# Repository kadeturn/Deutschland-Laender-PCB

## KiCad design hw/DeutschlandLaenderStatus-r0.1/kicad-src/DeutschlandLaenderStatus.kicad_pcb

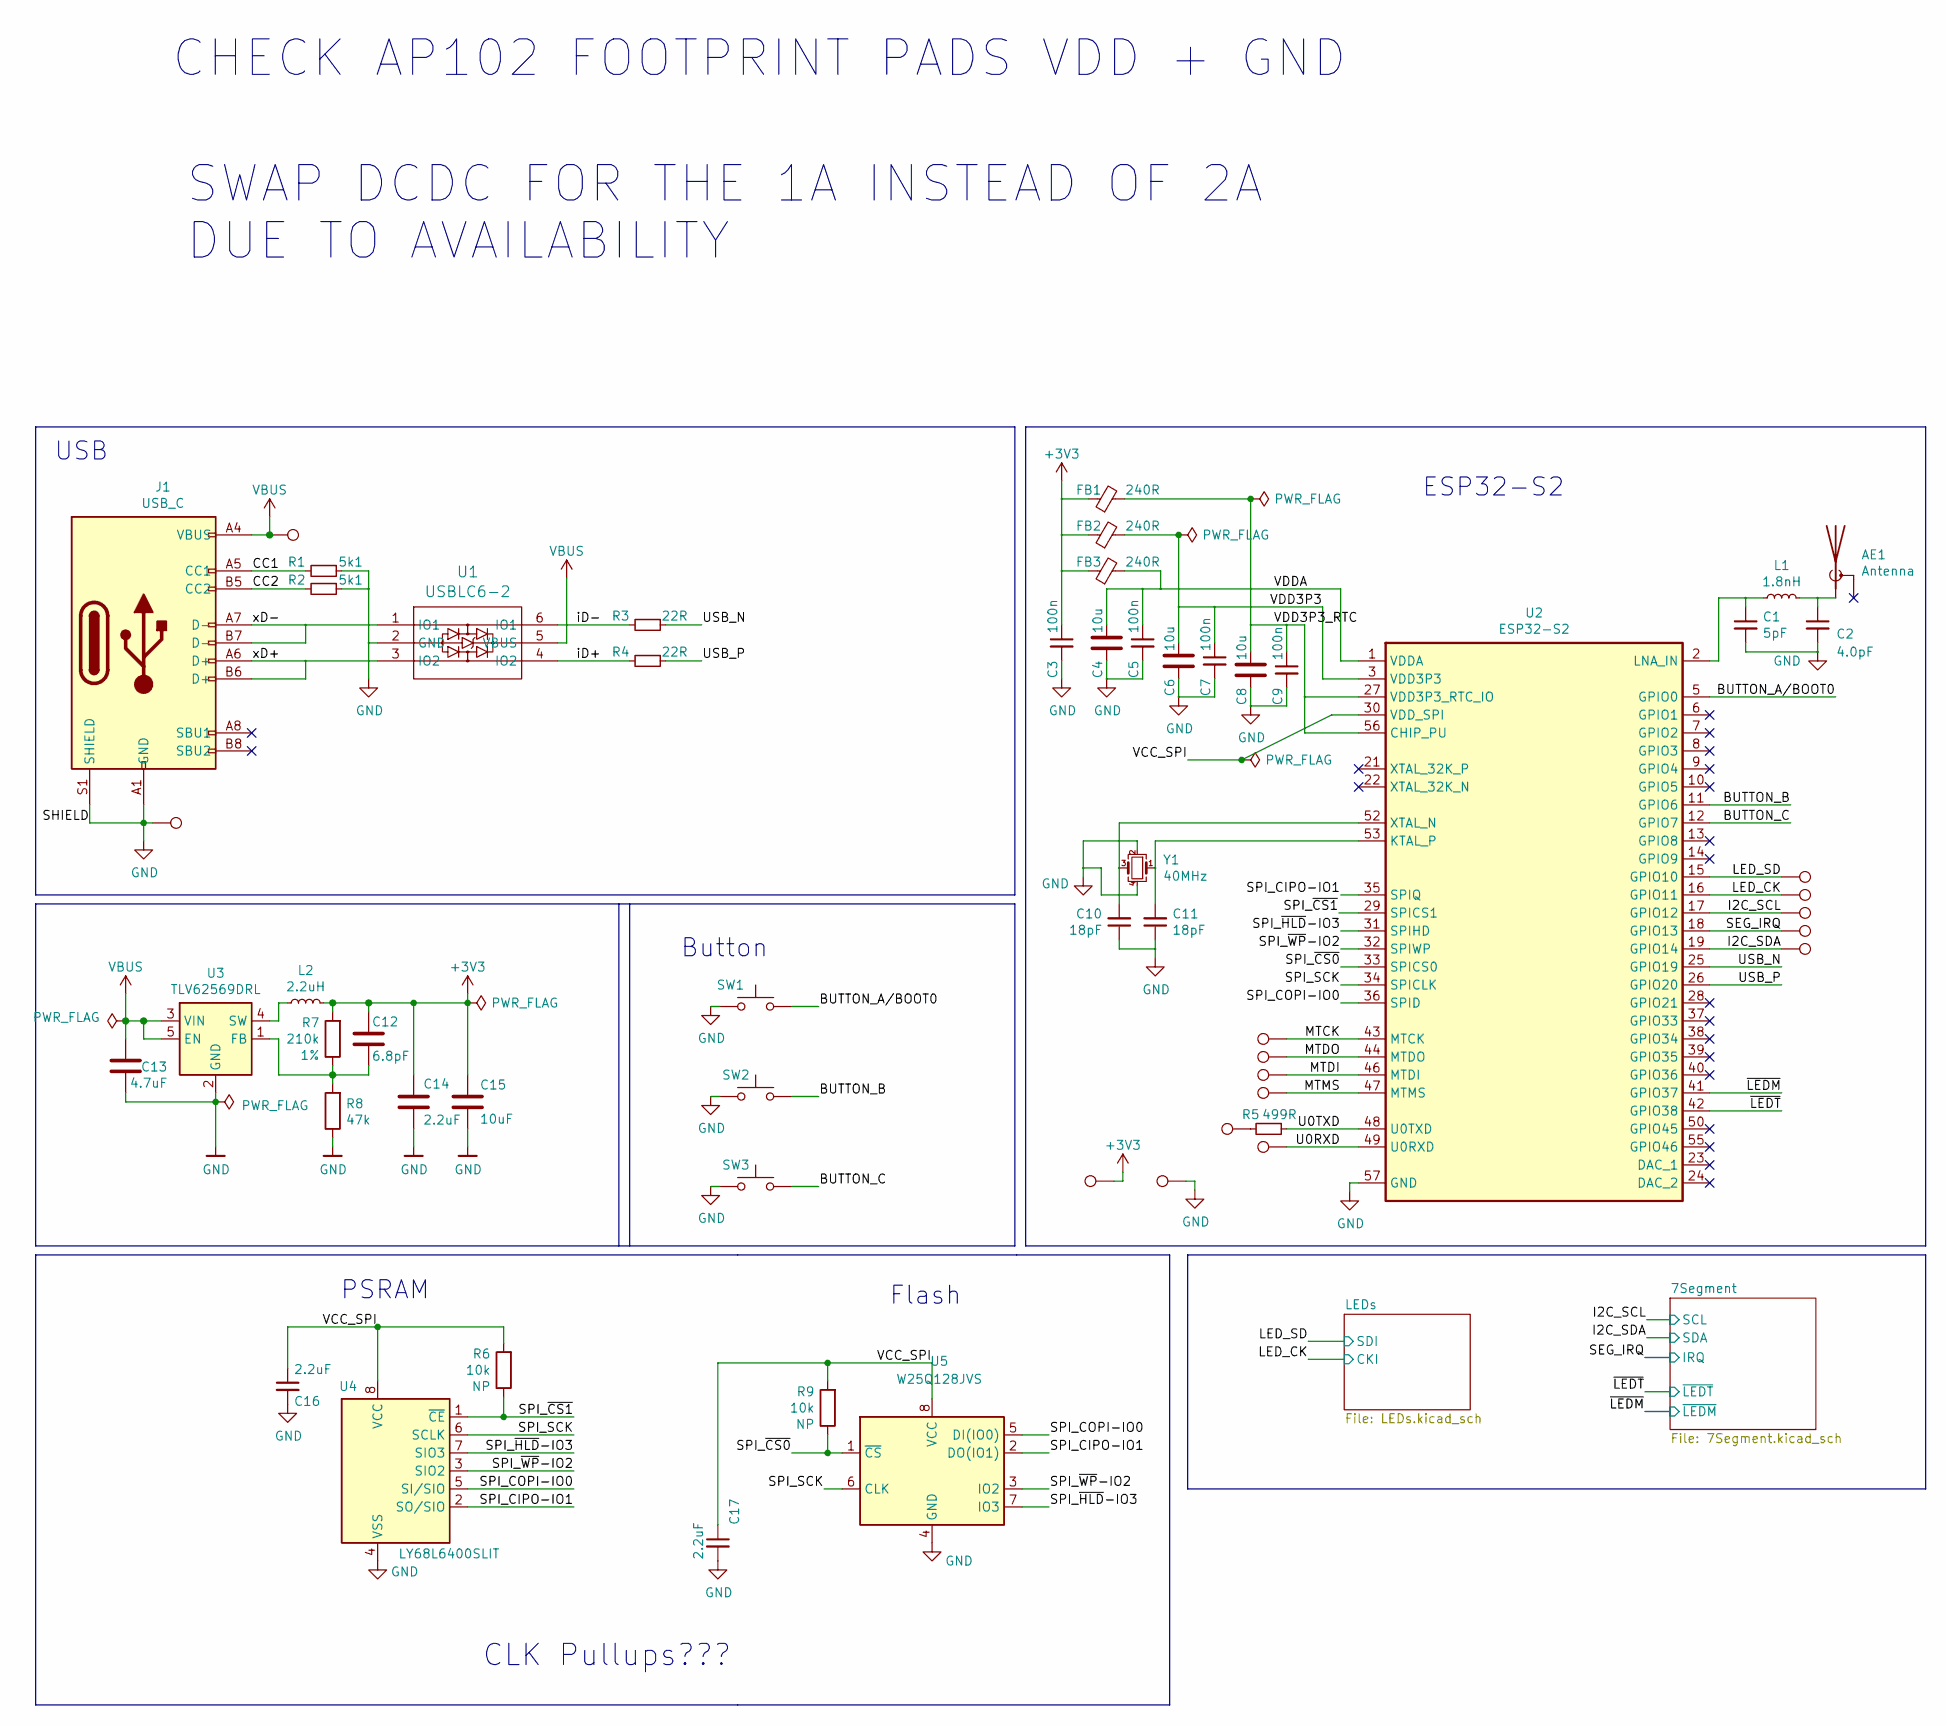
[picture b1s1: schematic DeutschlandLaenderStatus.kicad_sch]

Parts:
AE1: Antenna; Ant_3216
C1: 5pF; C_0402_1005Metric
C2: 4.0pF; C_0402_1005Metric
C3, C5, C7, C9: 100n; C_0402_1005Metric
C4, C6, C8: 10u; C_0603_1608Metric
C10, C11: 18pF; C_0402_1005Metric
C12: 6.8pF; C_0402_1005Metric
C13: 4.7uF; C_0402_1005Metric
C14, C16, C17: 2.2uF; C_0402_1005Metric
C15: 10uF; C_0603_1608Metric
FB1, FB2, FB3: 240R; L_0402_1005Metric
J1: USB_C; USB_C_Receptacle_HRO_TYPE-C-31-M-12
L1: 1.8nH; L_0402_1005Metric
L2: 2.2uH; L_0805_2012Metric
R1, R2: 5k1; R_0402_1005Metric
R3, R4: 22R; R_0402_1005Metric
R5: 499R; R_0402_1005Metric
R6, R9: 10k; R_0402_1005Metric
R7: 210k; R_0402_1005Metric
R8: 47k; R_0402_1005Metric
SW1, SW2, SW3: SW_Push; SW_SPST_B3U-3000P
TP1: VUSB; TestPoint_Pad_D1.5mm
TP2: LED_SD; TestPoint_Pad_D1.5mm
TP3: LED_CK; TestPoint_Pad_D1.5mm
TP4: 7SEG_SCL; TestPoint_Pad_D1.5mm
TP5: 7SEG_IRQ; TestPoint_Pad_D1.5mm
TP6: MTCK; TestPoint_Pad_D1.5mm
TP7: MTDO; TestPoint_Pad_D1.5mm
TP8: MTDI; TestPoint_Pad_D1.5mm
TP9: MTMS; TestPoint_Pad_D1.5mm
TP10: TX; TestPoint_Pad_D1.5mm
TP11: RX; TestPoint_Pad_D1.5mm
TP12: 3V3; TestPoint_Pad_D1.5mm
TP13, TP15: GND; TestPoint_Pad_D1.5mm
TP14: 7SEG_SDA; TestPoint_Pad_D1.5mm
U1: USBLC6-2; SOT-666
U2: ESP32-S2; QFN-56-1EP_7x7mm_P0.4mm_EP5.6x5.6mm
U3: TLV62569DRL; SOT-666
U4: LY68L6400SLIT; SOIC-8_3.9x4.9mm_P1.27mm
U5: W25Q128JVS; SOIC-8_5.23x5.23mm_P1.27mm
Y1: 40MHz; Crystal_SMD_4Pin_2.0x1.6mm

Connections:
+3V3: C3.1, C12.1, C14.1, C15.1, FB1.1, FB2.1, FB3.1, L2.2, R7.2, TP12.1; also elsewhere on the board
/BUTTON_A/BOOT0: SW1.2, U2.5 (GPIO0)
/BUTTON_B: SW2.2, U2.11 (GPIO6)
/BUTTON_C: SW3.2, U2.12 (GPIO7)
/CC1: J1.A5 (CC1), R1.2
/CC2: J1.B5 (CC2), R2.2
/I2C_SCL: TP4.1, U2.17 (GPIO12); also elsewhere on the board
/I2C_SDA: TP14.1, U2.19 (GPIO14); also elsewhere on the board
/LED_CK: TP3.1, U2.16 (GPIO11); also elsewhere on the board
/LED_SD: TP2.1, U2.15 (GPIO10); also elsewhere on the board
/MTCK: TP6.1, U2.43 (MTCK)
/MTDI: TP8.1, U2.46 (MTDI)
/MTDO: TP7.1, U2.44 (MTDO)
/MTMS: TP9.1, U2.47 (MTMS)
/SEG_IRQ: TP5.1, U2.18 (GPIO13); also elsewhere on the board
/SPI_CIPO-IO1: U2.35 (SPIQ), U4.2 (SO/SIO), U5.2 (DO(IO1))
/SPI_COPI-IO0: U2.36 (SPID), U4.5 (SI/SIO), U5.5 (DI(IO0))
/SPI_SCK: U2.34 (SPICLK), U4.6 (SCLK), U5.6 (CLK)
/SPI_~CS0: R9.1, U2.33 (SPICS0), U5.1 (~CS)
/SPI_~CS1: R6.1, U2.29 (SPICS1), U4.1 (~CE)
/SPI_~HLD-IO3: U2.31 (SPIHD), U4.7 (SIO3), U5.7 (IO3)
/SPI_~WP-IO2: U2.32 (SPIWP), U4.3 (SIO2), U5.3 (IO2)
/U0RXD: TP11.1, U2.49 (U0RXD)
/U0TXD: R5.1, U2.48 (U0TXD)
/USB_N: R3.1, U2.25 (GPIO19)
/USB_P: R4.1, U2.26 (GPIO20)
/VCC_SPI: C16.1, C17.1, R6.2, R9.2, U2.30 (VDD_SPI), U4.8 (VCC), U5.8 (VCC)
/VDD3P3: C6.1, C7.1, FB2.2, U2.3 (VDD3P3), U2.4 (VDD3P3)
/VDD3P3_RTC: C8.1, C9.1, FB1.2, U2.20 (VDD3P3_RTC), U2.27 (VDD3P3_RTC_IO), U2.45 (VDD3P3_CPU), U2.56 (CHIP_PU)
/VDDA: C4.1, C5.1, FB3.2, U2.1 (VDDA), U2.51 (VDDA), U2.54 (VDDA)
/iD+: R4.2, U1.4 (IO2)
/iD-: R3.2, U1.6 (IO1)
/xD+: J1.A6 (D+), J1.B6 (D+), U1.3 (IO2)
/xD-: J1.A7 (D-), J1.B7 (D-), U1.1 (IO1)
/~LEDM: U2.41 (GPIO37); also elsewhere on the board
/~LEDT: U2.42 (GPIO38); also elsewhere on the board
GND: C1.2, C2.2, C3.2, C4.2, C5.2, C6.2, C7.2, C8.2, C9.2, C10.1, C11.1, C13.2, C14.2, C15.2, C16.2, C17.2, J1.A1 (GND), J1.A12 (GND), J1.B1 (GND), J1.B12 (GND), J1.S1 (SHIELD), R1.1, R2.1, R8.1, SW1.1, SW2.1, SW3.1, TP13.1, TP15.1, U1.2 (GND), U2.57 (GND), U3.2 (GND), U4.4 (VSS), U5.4 (GND), Y1.2, Y1.4; also elsewhere on the board
unnamed: AE1.1 (A), C2.1, L1.2
unnamed: C1.1, L1.1, U2.2 (LNA_IN)
unnamed: C10.2, U2.52 (XTAL_N), Y1.3
unnamed: C11.2, U2.53 (KTAL_P), Y1.1
unnamed: C12.2, R7.1, R8.2, U3.1 (FB)
unnamed: L2.1, U3.4 (SW)
unnamed: R5.2, TP10.1
VBUS: C13.1, J1.A4 (VBUS), J1.A9 (VBUS), J1.B4 (VBUS), J1.B9 (VBUS), TP1.1, U1.5 (VBUS), U3.3 (VIN), U3.5 (EN); also elsewhere on the board

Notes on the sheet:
USB
CHECK AP102 FOOTPRINT PADS VDD + GND
SWAP DCDC FOR THE 1A INSTEAD OF 2A DUE TO AVAILABILITY
PSRAM
Button
CLK Pullups???
Flash
ESP32-S2

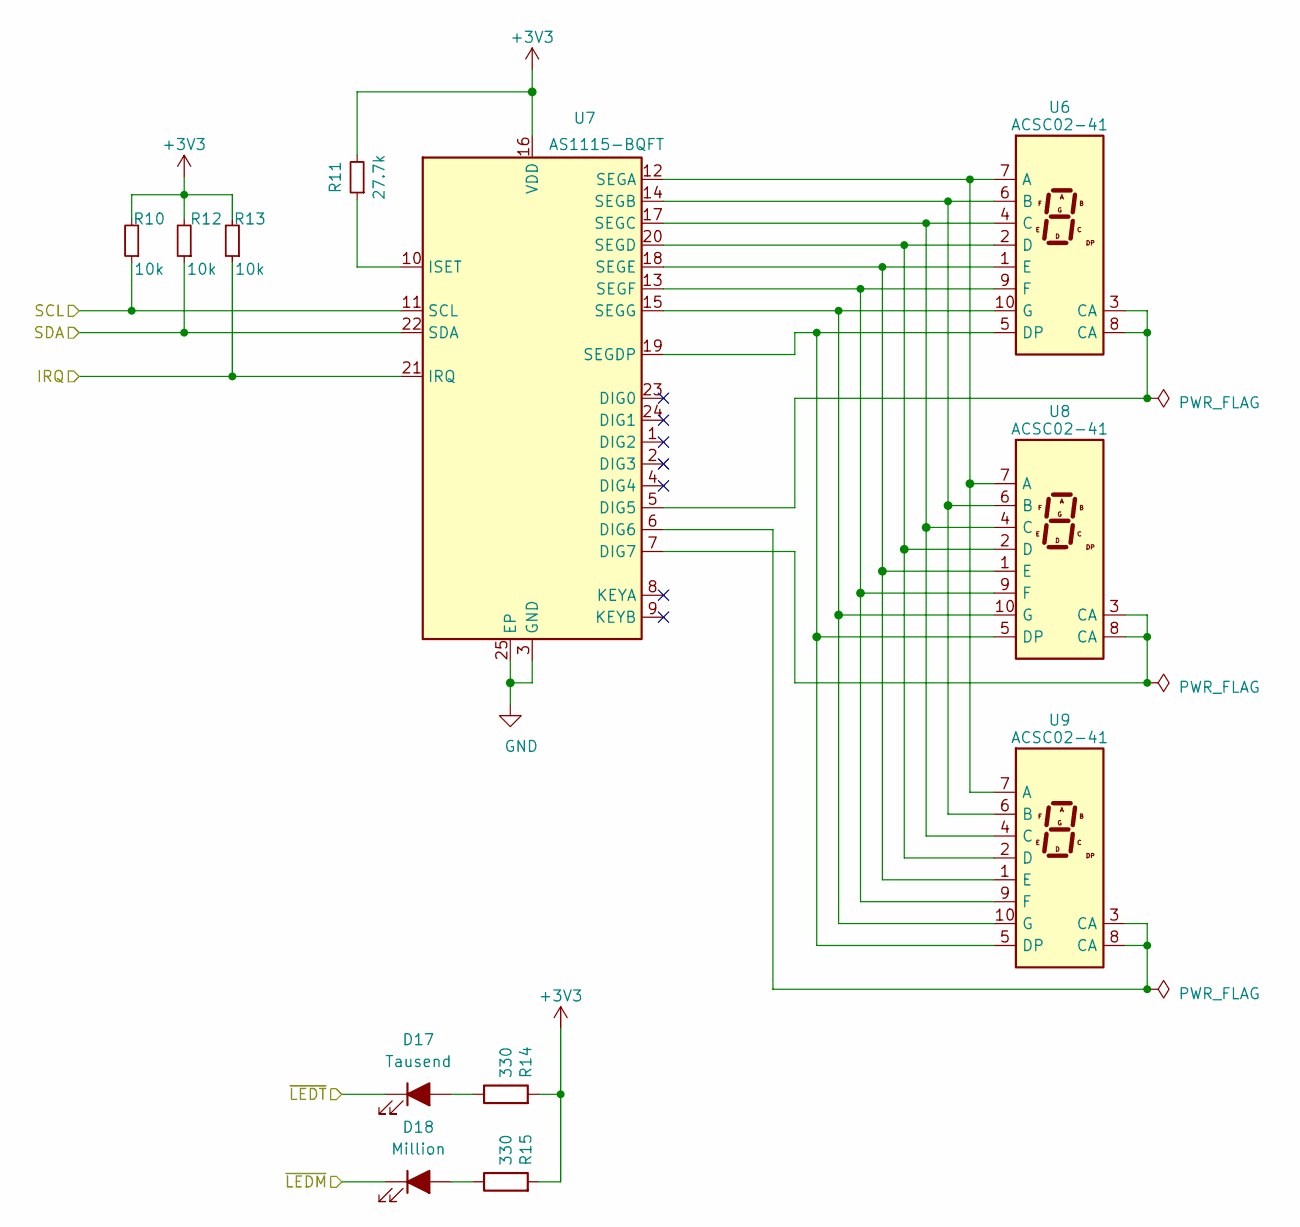
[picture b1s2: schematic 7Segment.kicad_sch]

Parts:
D17: Tausend; LED_0402_1005Metric
D18: Million; LED_0402_1005Metric
R10, R12, R13: 10k; R_0402_1005Metric
R11: 27.7k; R_0402_1005Metric
R14, R15: 330; R_0402_1005Metric
U6, U8, U9: ACSC02-41
U7: AS1115-BQFT; TQFN-24-1EP_4x4mm_P0.5mm_EP2.8x2.8mm_PullBack

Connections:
+3V3: R10.2, R11.2, R12.2, R13.2, R14.2, R15.2, U7.16 (VDD); also elsewhere on the board
/I2C_SCL: R10.1, U7.11 (SCL); also elsewhere on the board
/I2C_SDA: R12.1, U7.22 (SDA); also elsewhere on the board
/SEG_IRQ: R13.1, U7.21 (IRQ); also elsewhere on the board
/~LEDM: D18.1 (K); also elsewhere on the board
/~LEDT: D17.1 (K); also elsewhere on the board
GND: U7.3 (GND), U7.25 (EP); also elsewhere on the board
unnamed: D17.2 (A), R14.1
unnamed: D18.2 (A), R15.1
unnamed: R11.1, U7.10 (ISET)
unnamed: U6.1 (E), U7.18 (SEGE), U8.1 (E), U9.1 (E)
unnamed: U6.2 (D), U7.20 (SEGD), U8.2 (D), U9.2 (D)
unnamed: U6.3 (CA), U6.8 (CA), U7.5 (DIG5)
unnamed: U6.4 (C), U7.17 (SEGC), U8.4 (C), U9.4 (C)
unnamed: U6.5 (DP), U7.19 (SEGDP), U8.5 (DP), U9.5 (DP)
unnamed: U6.6 (B), U7.14 (SEGB), U8.6 (B), U9.6 (B)
unnamed: U6.7 (A), U7.12 (SEGA), U8.7 (A), U9.7 (A)
unnamed: U6.9 (F), U7.13 (SEGF), U8.9 (F), U9.9 (F)
unnamed: U6.10 (G), U7.15 (SEGG), U8.10 (G), U9.10 (G)
unnamed: U7.6 (DIG6), U9.3 (CA), U9.8 (CA)
unnamed: U7.7 (DIG7), U8.3 (CA), U8.8 (CA)

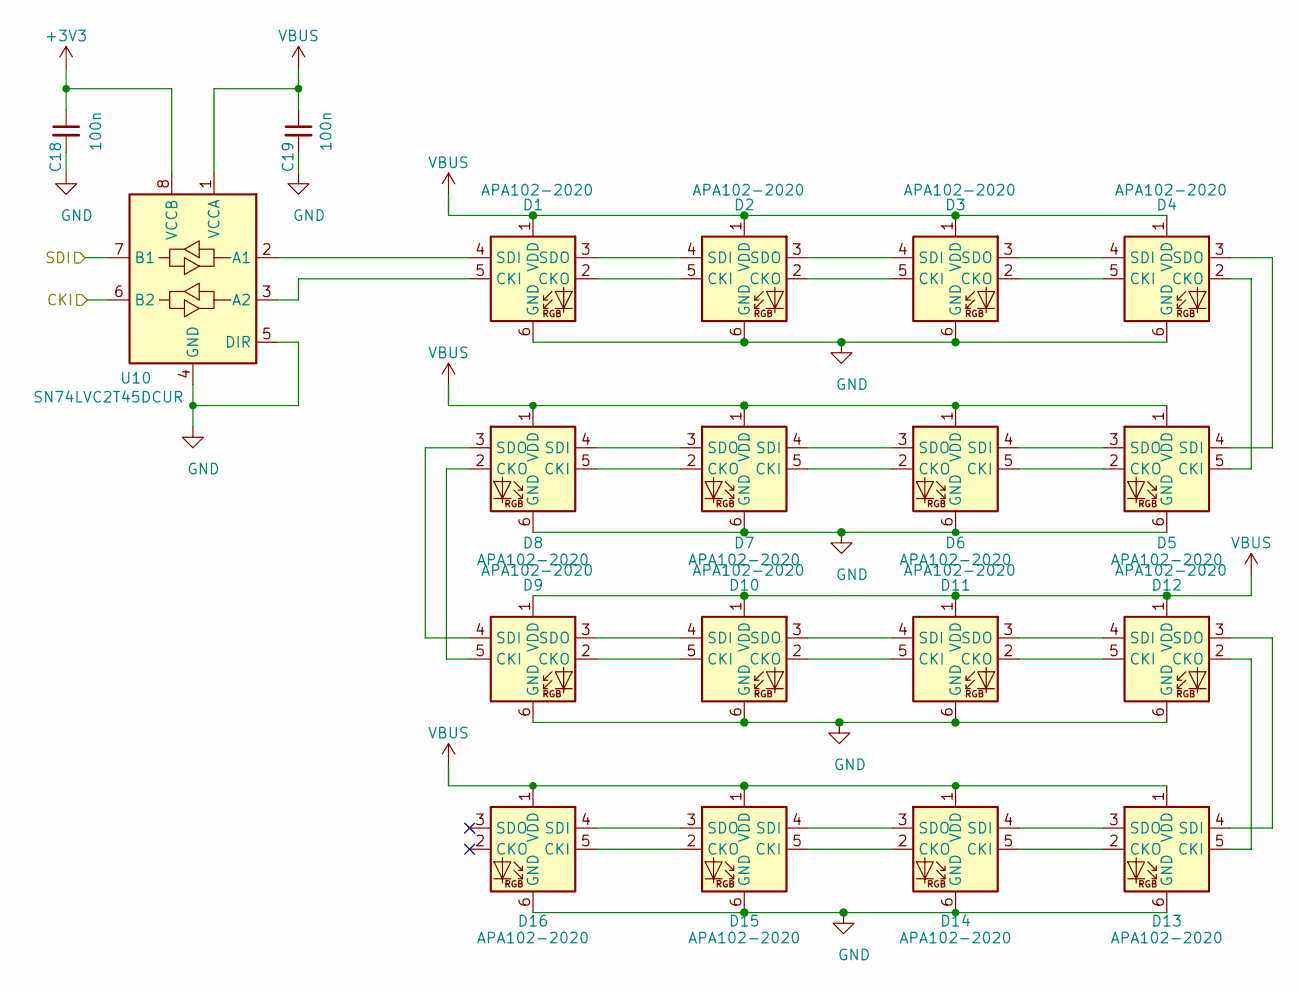
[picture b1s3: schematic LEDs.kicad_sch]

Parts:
C18, C19: 100n; C_0402_1005Metric
D1, D2, D3, D4, D5, D6, D7, D8, D9, D10, D11, D12, D13, D14, D15, D16: APA102-2020; LED-APA102-2020
U10: SN74LVC2T45DCUR; VSSOP-8_2.4x2.1mm_P0.5mm

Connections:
+3V3: C18.1, U10.8 (VCCB); also elsewhere on the board
/LED_CK: U10.6 (B2); also elsewhere on the board
/LED_SD: U10.7 (B1); also elsewhere on the board
GND: C18.2, C19.2, D1.6 (GND), D2.6 (GND), D3.6 (GND), D4.6 (GND), D5.6 (GND), D6.6 (GND), D7.6 (GND), D8.6 (GND), D9.6 (GND), D10.6 (GND), D11.6 (GND), D12.6 (GND), D13.6 (GND), D14.6 (GND), D15.6 (GND), D16.6 (GND), U10.4 (GND), U10.5 (DIR); also elsewhere on the board
unnamed: D1.2 (CKO), D2.5 (CKI)
unnamed: D1.3 (SDO), D2.4 (SDI)
unnamed: D1.4 (SDI), U10.2 (A1)
unnamed: D1.5 (CKI), U10.3 (A2)
unnamed: D2.2 (CKO), D3.5 (CKI)
unnamed: D2.3 (SDO), D3.4 (SDI)
unnamed: D3.2 (CKO), D4.5 (CKI)
unnamed: D3.3 (SDO), D4.4 (SDI)
unnamed: D4.2 (CKO), D5.5 (CKI)
unnamed: D4.3 (SDO), D5.4 (SDI)
unnamed: D5.2 (CKO), D6.5 (CKI)
unnamed: D5.3 (SDO), D6.4 (SDI)
unnamed: D6.2 (CKO), D7.5 (CKI)
unnamed: D6.3 (SDO), D7.4 (SDI)
unnamed: D7.2 (CKO), D8.5 (CKI)
unnamed: D7.3 (SDO), D8.4 (SDI)
unnamed: D8.2 (CKO), D9.5 (CKI)
unnamed: D8.3 (SDO), D9.4 (SDI)
unnamed: D10.2 (CKO), D11.5 (CKI)
unnamed: D10.3 (SDO), D11.4 (SDI)
unnamed: D9.3 (SDO), D10.4 (SDI)
unnamed: D9.2 (CKO), D10.5 (CKI)
unnamed: D11.2 (CKO), D12.5 (CKI)
unnamed: D11.3 (SDO), D12.4 (SDI)
unnamed: D12.2 (CKO), D13.5 (CKI)
unnamed: D12.3 (SDO), D13.4 (SDI)
unnamed: D13.2 (CKO), D14.5 (CKI)
unnamed: D13.3 (SDO), D14.4 (SDI)
unnamed: D14.2 (CKO), D15.5 (CKI)
unnamed: D14.3 (SDO), D15.4 (SDI)
unnamed: D15.2 (CKO), D16.5 (CKI)
unnamed: D15.3 (SDO), D16.4 (SDI)
VBUS: C19.1, D1.1 (VDD), D2.1 (VDD), D3.1 (VDD), D4.1 (VDD), D5.1 (VDD), D6.1 (VDD), D7.1 (VDD), D8.1 (VDD), D9.1 (VDD), D10.1 (VDD), D11.1 (VDD), D12.1 (VDD), D13.1 (VDD), D14.1 (VDD), D15.1 (VDD), D16.1 (VDD), U10.1 (VCCA); also elsewhere on the board

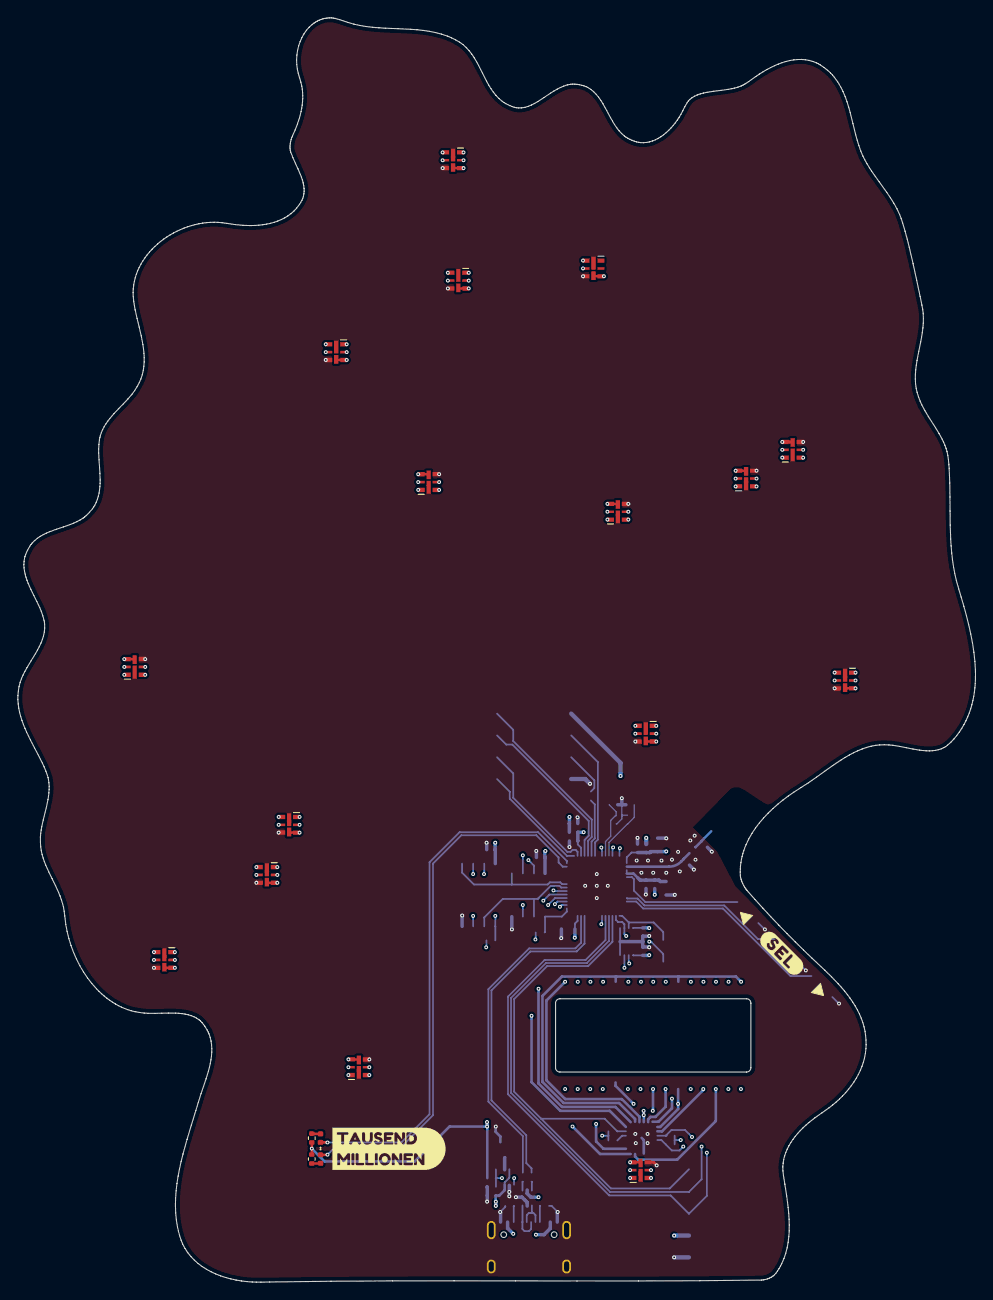
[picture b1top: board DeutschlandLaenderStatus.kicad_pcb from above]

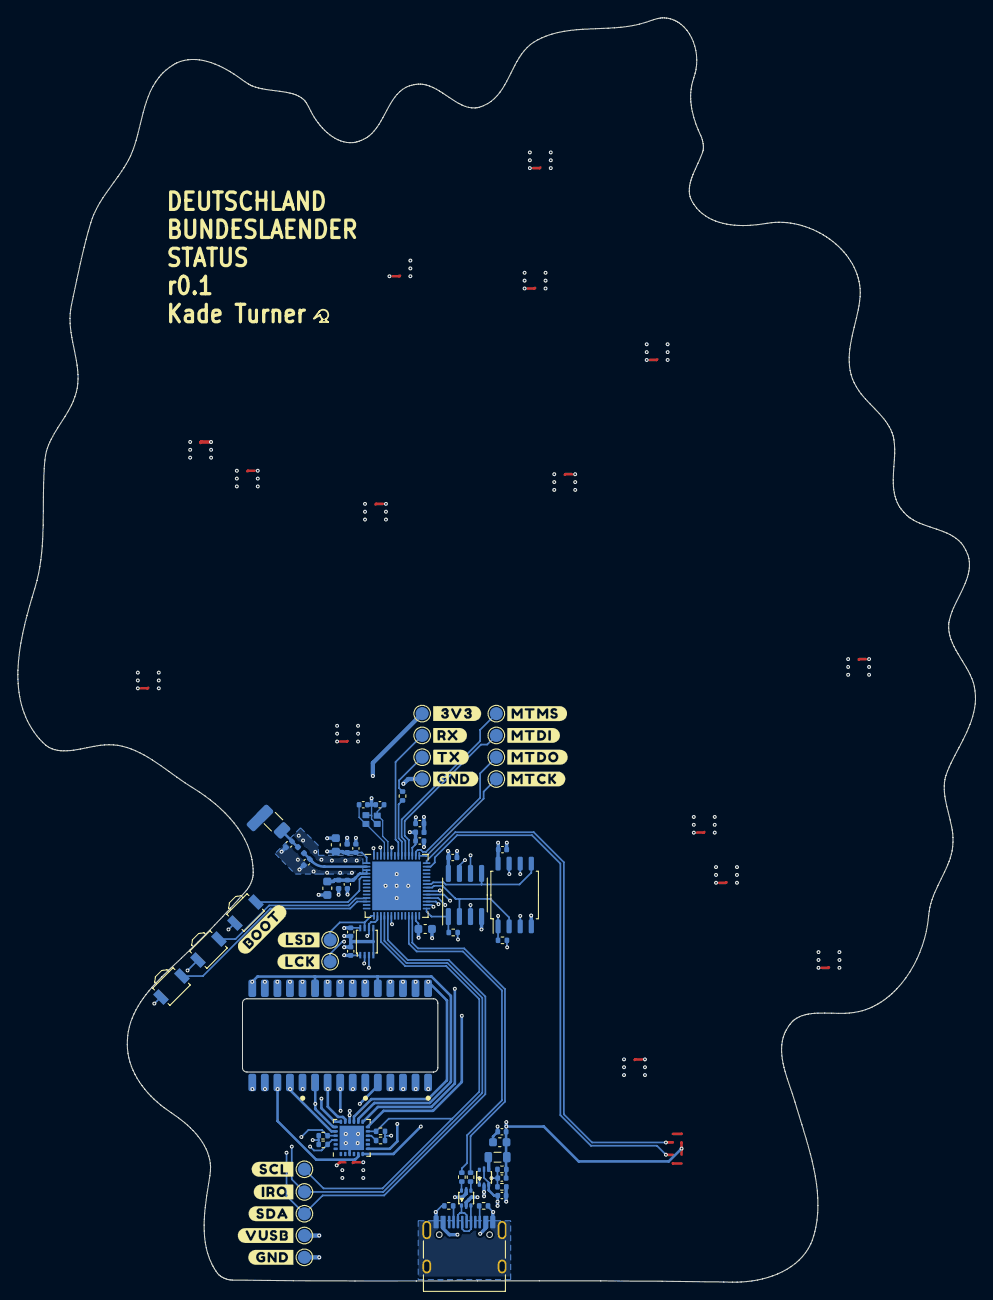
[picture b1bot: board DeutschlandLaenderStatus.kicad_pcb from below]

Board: 4 copper layers, 109.8 x 145.0 mm, 90 parts (65 on the bottom side), 91 nets.

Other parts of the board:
Ref**: Val**; outlined_v2
kibuzzard-6108F752: G***; kibuzzard-6108F752

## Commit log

2021-01-20 Add license
2021-01-20 initial schematic + doc upload
2021-01-20 Removed submodule hw\lib
2021-01-20 remove sub module
2021-01-20 added lib
2021-01-22 added 7segment display
2021-01-24 Layout complete
    Need to added Map Outline still
2021-01-25 initial artwork created
2021-02-01 added artwork
2021-02-07 updated to PCB outline
2021-05-03 PCB note updates
2021-07-15 small changes to track placement
2021-07-27 V1 release
2021-08-03 Altered silkscreen for V1
2021-08-17 Manufacture export
2021-08-22 added correct flash memory datasheet, deleted old version
